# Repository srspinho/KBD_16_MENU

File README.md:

# RP2040 HID Remapper & System Monitor v3 ⌨️📺

Este projeto transforma um **Raspberry Pi Pico (RP2040 ou RP2350)** num intermediário entre o teclado USB e o PC. O teclado físico é ligado no Pico, e o Pico se apresenta ao PC como teclado + teclas de mídia + mouse. No caminho, ele remapeia atalhos, conta e analisa a digitação e mostra tudo num display TFT colorido de 160x80. Um joystick de 5 botões controla o menu.

## 🆕 Novidades da versão 3

**Correções**
- Menu: agora todos os itens dos submenus podem ser editados. Antes, só o primeiro de cada submenu funcionava.
- A contagem de setas, F8–F12, teclado numérico e `\` estava errada (deslocamento de bits ≥ 64) e foi corrigida.
- Fim das teclas "presas" no PC: os reports passam por uma fila e nenhum é descartado quando o USB está ocupado.
- Os dois núcleos não usam mais a mesma pilha USB ao mesmo tempo, o que podia travar o dispositivo.
- Os LEDs (Caps/Num Lock) são reaplicados quando o teclado é reconectado, e a desconexão do teclado agora é detectada.
- Remapeamento estável: soltar o AltGr antes do R não digita mais um "r".
- Screensavers sem desenho duplicado, sem cintilação e com as bolas sem acelerar até sumir. O Game of Life reinicia quando estabiliza.
- "Intervalo" do anti-bloqueio e "Brilho" passaram a funcionar. O escurecimento automático foi implementado.
- Configurações gravadas com versão + CRC, e só ao sair do menu (menos desgaste da flash e menos pausas no USB).
- Watchdog: se algo travar, o dispositivo reinicia sozinho.

**Novas funções**
- Páginas no monitor: Principal, Estatísticas, Top teclas, Pomodoro e Relógio.
- Total de teclas guardado na flash, contagem do dia, KPM (teclas por minuto) e recorde.
- Ranking das teclas mais usadas.
- Indicadores de Caps Lock e Num Lock na tela.
- Pomodoro, lembrete de pausa (prevenção de LER) e buzzer opcional.
- Camada Fn: com Caps Lock segurado, H/J/K/L viram setas, 1–0 viram F1–F10, etc.
- Macros: um atalho digita um texto.
- Relógio: ajuste pelo menu ou módulo RTC DS3231 opcional.
- Novos screensavers: Pong (simulação do jogo clássico, no lugar das Bolas), Estrelas em dobra espacial, foguetes nos Fogos e Relógio.
- Menu com auto-repetição acelerada, barra de rolagem, confirmação para ações perigosas e fechamento automático.
- "Modo gravação": entra no BOOTSEL pelo menu, sem precisar apertar o botão da placa.
- Testes automáticos da lógica do teclado, que rodam no PC (`test/host`).

## 🎮 Controles

| Onde | Botão | Ação |
|---|---|---|
| Monitor | **OK** | Abre o menu |
| Monitor | **← / →** | Troca de página |
| Página Pomodoro | **↑ / ↓** | Inicia/pausa · zera |
| Screensaver / tela escurecida | qualquer | Só acorda a tela |
| Menu | **↑ / ↓** | Move (segure para repetir) |
| Menu | **OK / →** | Entra · edita · liga/desliga · confirma |
| Menu | **←** | Volta (na raiz, fecha o menu) |
| Editando valor | **↑ / ↓** | Altera (segure para acelerar) |
| Editando valor | **OK / ← / →** | Termina a edição |

O menu fecha sozinho após 30 s sem uso e só grava na flash se algo mudou.

## 📋 Menu

```
CONFIGURACOES
├─ Screensaver   Tipo (lista) · Iniciar apos (min, 0 = nunca) · Trocar a cada (s)
│                Velocidade · Asteroides · Cores (%)
├─ Tela          Brilho · Brilho ocioso · Escurecer apos (s) · Girar 180
├─ Produtividade Anti-bloqueio · Intervalo (s) · Pomodoro >/|| · Pomodoro zerar
│                Foco (min) · Pausa (min) · Lembrete pausa (min, 0 = off)
├─ Teclado       Remapear · Camada Fn · Sinc. volume · Volume inicial
├─ Relogio       Hora · Minuto
├─ Estatisticas  Zerar sessao · Zerar tudo
├─ Sistema       Sobre · Reiniciar · Restaurar padrao · Modo gravacao
└─ Sair
```

## 🚀 Funcionalidades

### Teclado
- **Remapeamentos** (tabela em `keymap.cpp`):
  - `AltGr + R` → `\`
  - `AltGr + M` → `Ctrl + Shift + M` (microfone do Teams)
- **Macros:** um atalho digita um texto. Para criar uma, descomente o exemplo em `keymap.cpp`. Aceita letras, números, espaço, Enter, Tab e `. , - _ = + ! @ # $ % & * ( )`, que ficam na mesma posição no ABNT2 e no US.
- **Camada Fn** (desligada por padrão; ative em *Teclado > Camada Fn*). Segurando **Caps Lock**:
  - H/J/K/L → setas
  - Y/O → Home/End
  - U/N → PgUp/PgDn
  - Backspace → Delete
  - 1…0, -, = → F1…F12

  Um toque rápido no Caps Lock continua ligando e desligando o Caps.
- O teclado e o encoder de volume são lidos pelo descritor HID, o que deve servir para mais modelos de teclado.

### Monitor (páginas ← / →)
1. **Principal:**
   - Teclas de hoje (ou da sessão, se a hora não estiver ajustada)
   - KPM e gráfico dos últimos 60 s com escala automática
   - Barra de volume (e aviso de "MUDO")
   - LEDs Caps/Num, hora e barra de progresso do Pomodoro
2. **Estatísticas:** sessão, hoje, total (guardado na flash), KPM e recorde, tempo digitando e tempo ligado.
3. **Top teclas:** as 5 teclas mais usadas desde sempre. Só a quantidade de cada tecla é guardada, nunca a ordem do que foi digitado.
4. **Pomodoro:** contagem regressiva, fase (foco/pausa) e ciclos.
5. **Relógio.**

### Produtividade
- **Anti-bloqueio:** sem digitação pelo intervalo configurado, move o mouse 1 px e volta.
  > ⚠️ Em computadores corporativos, impedir o bloqueio de tela pode contrariar a política de segurança. Use com responsabilidade; a opção pode ser desligada.
- **Pomodoro** com alertas na tela (e no buzzer, se instalado).
- **Lembrete de pausa:** avisa depois de X minutos de digitação contínua. Cinco minutos sem digitar contam como pausa.

### Screensavers
Atari (arco-íris), Pong, Asteroides, Estrelas, Vida (Game of Life), Matrix, Pac-Man, Fogos, Aquário, Relógio, ou **Todos** (rotação automática).

### Relógio ⏰
O dispositivo **não consegue obter a hora do PC sem um programa rodando no PC**, porque o protocolo de teclado/mouse (HID) não transporta data e hora. Por isso há duas opções:
1. **Ajuste manual** em *Menu > Relogio*. A hora é mantida enquanto o dispositivo estiver energizado; se ele for desligado da USB, é preciso ajustar de novo.
2. **Módulo RTC DS3231** (opcional, barato, com bateria CR2032). É detectado sozinho no boot e mantém a hora mesmo desligado. Ao ajustar a hora pelo menu, o módulo também é atualizado.

## 🛠️ Hardware

### Placa de circuito impresso (KiCad)

A pasta [`hardware/`](hardware/README.md) tem o projeto KiCad completo de uma placa-base para o **Waveshare RP2350-Zero** (ou RP2040-Zero). Ela inclui:
- USB-A do teclado com fusível e proteção ESD;
- soquete do LCD e do joystick;
- RTC DS3231 com bateria;
- buzzer.

Também traz os Gerbers prontos para encomendar, a lista de componentes e o esquemático em PDF.

### Componentes

- **Microcontrolador:** RP2040 (testado no Waveshare RP2040-Zero) ou RP2350 (Waveshare RP2350-Zero).
- **Display:** TFT ST7735 0,96" 160x80 (SPI).
- **USB host:** conector USB-C/A para o teclado via PIO-USB.
- **Joystick de 5 botões** (4 direções + OK), com o pino comum no GND.
- *Opcional:* módulo RTC DS3231 e buzzer passivo.

### Pinagem

| Componente | GPIO | Observação |
|---|---|---|
| TFT_MISO | 12 | configurado no TFT_eSPI |
| TFT_MOSI (SDA) | 11 | |
| TFT_SCLK (SCL) | 10 | |
| TFT_CS | 13 | |
| TFT_DC | 14 | |
| TFT_RST | 15 | |
| **TFT_BLK** | **7** | Para o brilho funcionar. Ligado no 3V3, o brilho fica sempre no máximo (nesse caso use `PIN_BACKLIGHT -1`). |
| USB Host D+ | 0 | |
| USB Host D- | 1 | sempre D+ + 1 |
| USB VCC / GND | 5V / GND | |
| JOY_UP | 2 | |
| JOY_DOWN | 3 | |
| JOY_OK | 4 | |
| JOY_RIGHT | 5 | |
| JOY_LEFT | 6 | |
| RTC SDA *(opcional)* | 26 | I2C1 |
| RTC SCL *(opcional)* | 27 | I2C1 |
| Buzzer *(opcional)* | 8 | via transistor; `PIN_BUZZER` em `kbd_config.h` (-1 = sem buzzer) |

Todos os pinos (exceto os do display) ficam em **`kbd_config.h`**.

## 💻 Como compilar

1. Instale o core **Raspberry Pi Pico/RP2040/RP2350** (Earle Philhower) no Arduino IDE.
2. Bibliotecas:
   - [Pico-PIO-USB](https://github.com/sekigon-gonnoc/Pico-PIO-USB): USB host via PIO
   - [TFT_eSPI](https://github.com/Bodmer/TFT_eSPI): use um *User_Setup* para ST7735 160x80 (ex.: `Setup43_ST7735.h`) com os pinos da tabela acima
   - O Adafruit TinyUSB já vem com o core.
3. Em *Ferramentas*:
   - **Placa:** Waveshare RP2350 Zero (ou Waveshare RP2040 Zero)
   - **CPU Speed:** **120 MHz** (múltiplo de 12 MHz, exigido pelo USB host). No RP2350 o padrão é 150 MHz, que **não funciona**. Com um clock inválido, a tela mostra um erro explicando.
   - **USB Stack:** Adafruit TinyUSB
4. A pasta do projeto precisa ter o **mesmo nome do `.ino`**: `KBD_COLOR_16_MENU`.
5. Grave e conecte o teclado na porta USB host.

Para atualizar o firmware depois, use *Menu > Sistema > Modo gravacao* e copie o `.uf2` para a unidade `RPI-RP2`.

## 🧩 Estrutura do código

| Arquivo | Função |
|---|---|
| `KBD_COLOR_16_MENU.ino` | Só chama `app_*` (core 0) e `bridge_*` (core 1) |
| `kbd_config.h` | Pinos e opções de hardware |
| `usb_bridge.*` | **Core 1:** USB host, remapeamento, camada Fn, macros, fila de envio ao PC, LEDs |
| `shared.*` | Filas entre os núcleos (sem travas) |
| `keymap.*` | Tabelas de remapeamento, macros, camada e nomes das teclas |
| `app.*` | **Core 0:** lógica principal, anti-bloqueio, volume, alertas, watchdog |
| `ui.*` | Páginas do monitor, alertas e avisos |
| `menu.*` | Menu orientado a dados |
| `screensavers.*` | Screensavers numa tabela (adicionar um = uma linha) |
| `settings.*` | Preferências e armazenamento na flash (versão + CRC) |
| `stats.*` | Contagem, KPM, ranking de teclas |
| `pomodoro.*`, `clock.*`, `buttons.*`, `display.*` | Pomodoro, relógio/RTC, joystick, display/cores |
| `test/host/` | Testes que rodam no PC (`make`) |

## 🧪 Testes

A lógica do teclado (remapeamento, camada Fn, macros, fila sem perda, LEDs, mídia) e as estatísticas têm testes que rodam no PC, sem hardware:

```
cd test/host
make
```

## ⚠️ Limitações conhecidas

- **Volume:** o PC não informa o volume por HID. No boot, o volume do PC é levado a um valor conhecido (*Teclado > Volume inicial*), e a barra acompanha o encoder do teclado. Mudanças feitas pelo próprio PC não aparecem.
- **Hora:** veja a seção do relógio. Sem o RTC, a contagem "hoje" recomeça quando o dispositivo é desligado. O total e o ranking ficam na flash.
- Teclados no modo *boot* (6 teclas simultâneas) são suportados. Teclados que só funcionam em NKRO podem precisar estar no modo 6KRO.

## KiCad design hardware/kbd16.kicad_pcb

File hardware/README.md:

# Placa KBD16 (KiCad)

Placa-base para o **Waveshare RP2350-Zero**, que também aceita o **RP2040-Zero** (mesma pinagem). Ela junta numa só placa:

- a porta USB-A do teclado, com proteção;
- o LCD 0,96" 80x160;
- o joystick de 5 vias;
- o relógio RTC, com bateria;
- o buzzer.

A pinagem é a mesma do firmware (`kbd_config.h`), então não é preciso mudar nada no código.

| Frente | Verso |
|---|---|
|  |  |

- **Tamanho:** 86 × 52 mm, 2 camadas, cantos arredondados, 4 furos M3.
- **Regras:** trilhas de 0,25 mm (sinais) e 0,4–0,6 mm (alimentação), folga de 0,2 mm, vias de 0,8/0,4 mm. Qualquer fábrica comum (JLCPCB, PCBWay etc.) fabrica sem custo extra.
- **Planos de GND** nas duas camadas.
- **DRC** (verificação de regras do KiCad): sem erros e sem conexões faltando. Os únicos avisos são da serigrafia do USB-A, que fica para fora da borda de propósito.
- **Esquemático e PCB sincronizados** (verificado automaticamente).

## Arquivos

| Arquivo | Conteúdo |
|---|---|
| `kbd16.kicad_pro` / `.kicad_sch` / `.kicad_pcb` | Projeto KiCad (abre no KiCad 7 ou 8) |
| `lib/` | Símbolo e footprint do RP2350-Zero e footprint do soquete do LCD |
| `fab/kbd16_gerbers.zip` | **Gerbers + furação: é o arquivo que se envia para a fábrica** |
| `fab/kbd16_bom.csv` | Lista de componentes |
| `fab/kbd16_esquematico.pdf` | Esquemático em PDF |
| `fab/kbd16_posicao.csv` | Posição dos componentes (só para montagem pela fábrica) |
| `img/` | Imagens da placa |
| `tools/` | Scripts que geram tudo a partir de `tools/design.py` |

## Ligações (iguais às do firmware)

| Função | GPIO | Na placa |
|---|---|---|
| USB host D+ / D- (teclado) | GP0 / GP1 | J1 (USB-A), via R1/R2 (22 Ω) e proteção ESD U2 |
| Joystick cima / baixo / OK / dir / esq | GP2 / GP3 / GP4 / GP5 / GP6 | J3, com pull-ups de 10 kΩ (R4–R8) |
| Backlight do LCD (BLK) | GP7 | J2 pino 8, via R3 (100 Ω) |
| Buzzer | GP8 | Q1 + BZ1 (alimentado em 5 V) |
| LCD SCL / SDA / CS / DC / RES | GP10 / GP11 / GP13 / GP14 / GP15 | J2 |
| RTC SDA / SCL (I2C1) | GP26 / GP27 | U3 (DS3231), pull-ups de 4,7 kΩ |
| Livres | GP9, GP12, GP28, GP29 | (expansão futura) |

O 5 V do teclado sai do pino 5V do módulo (que vem do USB-C do PC) e passa pelo fusível rearmável F1 (500 mA).

## Montagem

Ordem sugerida, do componente mais baixo para o mais alto:

1. **SMD:**
   - resistores e capacitores 0805 (ilhas maiores, próprias para solda manual);
   - U2 (SOT-23-6), Q1 (SOT-23), D1 (SOD-123), F1 (1206);
   - U3 (SOIC-16), se for usar o RTC.
2. **Suporte da bateria BT1** (CR1220), se for usar o RTC.
3. **Barras fêmea:**
   - para o módulo: 2× 1x9 nas laterais e 1× 1x5 na fileira de baixo (GP9–GP13);
   - J2 (1x8) para o LCD;
   - J3 (1x6) para o joystick.

   Se preferir, solde o módulo direto na placa com barras macho, sem as fêmeas.
4. **USB-A J1 e buzzer BZ1** (THT).
5. **Módulo RP2350-Zero** com o USB-C virado para a borda de trás, onde está escrito *USB-C*.
6. **LCD:** encaixe no J2 com o display para cima, cobrindo a área marcada. A ordem dos pinos está na serigrafia: `GND VCC SCL SDA RES DC CS BLK`.

As partes opcionais podem ficar de fora sem afetar o resto:

| Opcional | Peças | Sem ela |
|---|---|---|
| **RTC** | U3, BT1, C3, R9, R10 | A hora é ajustada pelo menu e se perde ao desligar |
| **Buzzer** | BZ1, Q1, R11, R12, D1 | Os alertas aparecem só na tela |

> Se montar o U3, coloque a bateria: o DS3231 não deve ficar com o pino VBAT solto.

## ⚠️ Confira antes de encomendar

Alguns dados vieram de bibliotecas e fichas genéricas e não dá para confirmar sem as peças na mão. Imprima o PDF da placa em escala 1:1 e encoste as peças no papel:

1. **Módulo RP2350-Zero:** posição dos furos. A fileira de baixo (GP9–GP13) fica na mesma linha dos últimos pinos laterais.
2. **LCD:** a ordem dos 8 pinos do seu módulo (alguns fabricantes trocam) e o tamanho. O contorno de 30 × 24 mm é aproximado e está desenhado na camada F.Fab.
3. **Joystick:** a placa tem uma barra 1x6 na ordem `GND CIMA BAIXO ESQ DIR OK`. Ligue o comum do seu joystick no GND e cada direção no pino correspondente.
4. **USB-A:** footprint do Molex 67643 (THT horizontal, abas a 13,1 mm). A maioria das "USB-A fêmea 90° DIP" genéricas é compatível, mas confira as abas.

## Como encomendar

1. Envie `fab/kbd16_gerbers.zip` para a fábrica (ex.: JLCPCB → *Add gerber file*).
2. Opções:
   - 2 camadas, FR-4, 1,6 mm;
   - qualquer cor de máscara;
   - HASL (com ou sem chumbo).
   As demais podem ficar no padrão.
3. Os componentes estão em `fab/kbd16_bom.csv`. Todos são comuns: LCSC, Mouser, AliExpress etc.

## Firmware

- **Placa:** Waveshare RP2350 Zero.
- **USB Stack:** Adafruit TinyUSB.
- **CPU Speed: 120 MHz.** O padrão do RP2350 (150 MHz) **não funciona** com o USB host. Se esquecer, o firmware mostra um aviso na tela.
- O buzzer já está configurado no GP8 (`PIN_BUZZER` em `kbd_config.h`).

## Alterar a placa

Tudo é gerado a partir de `tools/design.py` (componentes, ligações e posições):

```
cd hardware/tools
python3 build_all.py
```

O script refaz em sequência:
- a biblioteca e o esquemático;
- a conferência entre os dois;
- a PCB e o roteamento;
- o DRC;
- os arquivos de fabricação e as imagens.

Ele precisa do KiCad 7 (`kicad-cli` e o módulo Python `pcbnew`); as imagens usam Node + Playwright e são opcionais.

O roteamento é feito por um roteador próprio e simples (`tools/router.py`, A* em grade). Se preferir, abra a placa no KiCad e refaça trilhas à mão: a partir daí, edite direto no KiCad em vez de rodar os scripts de novo.

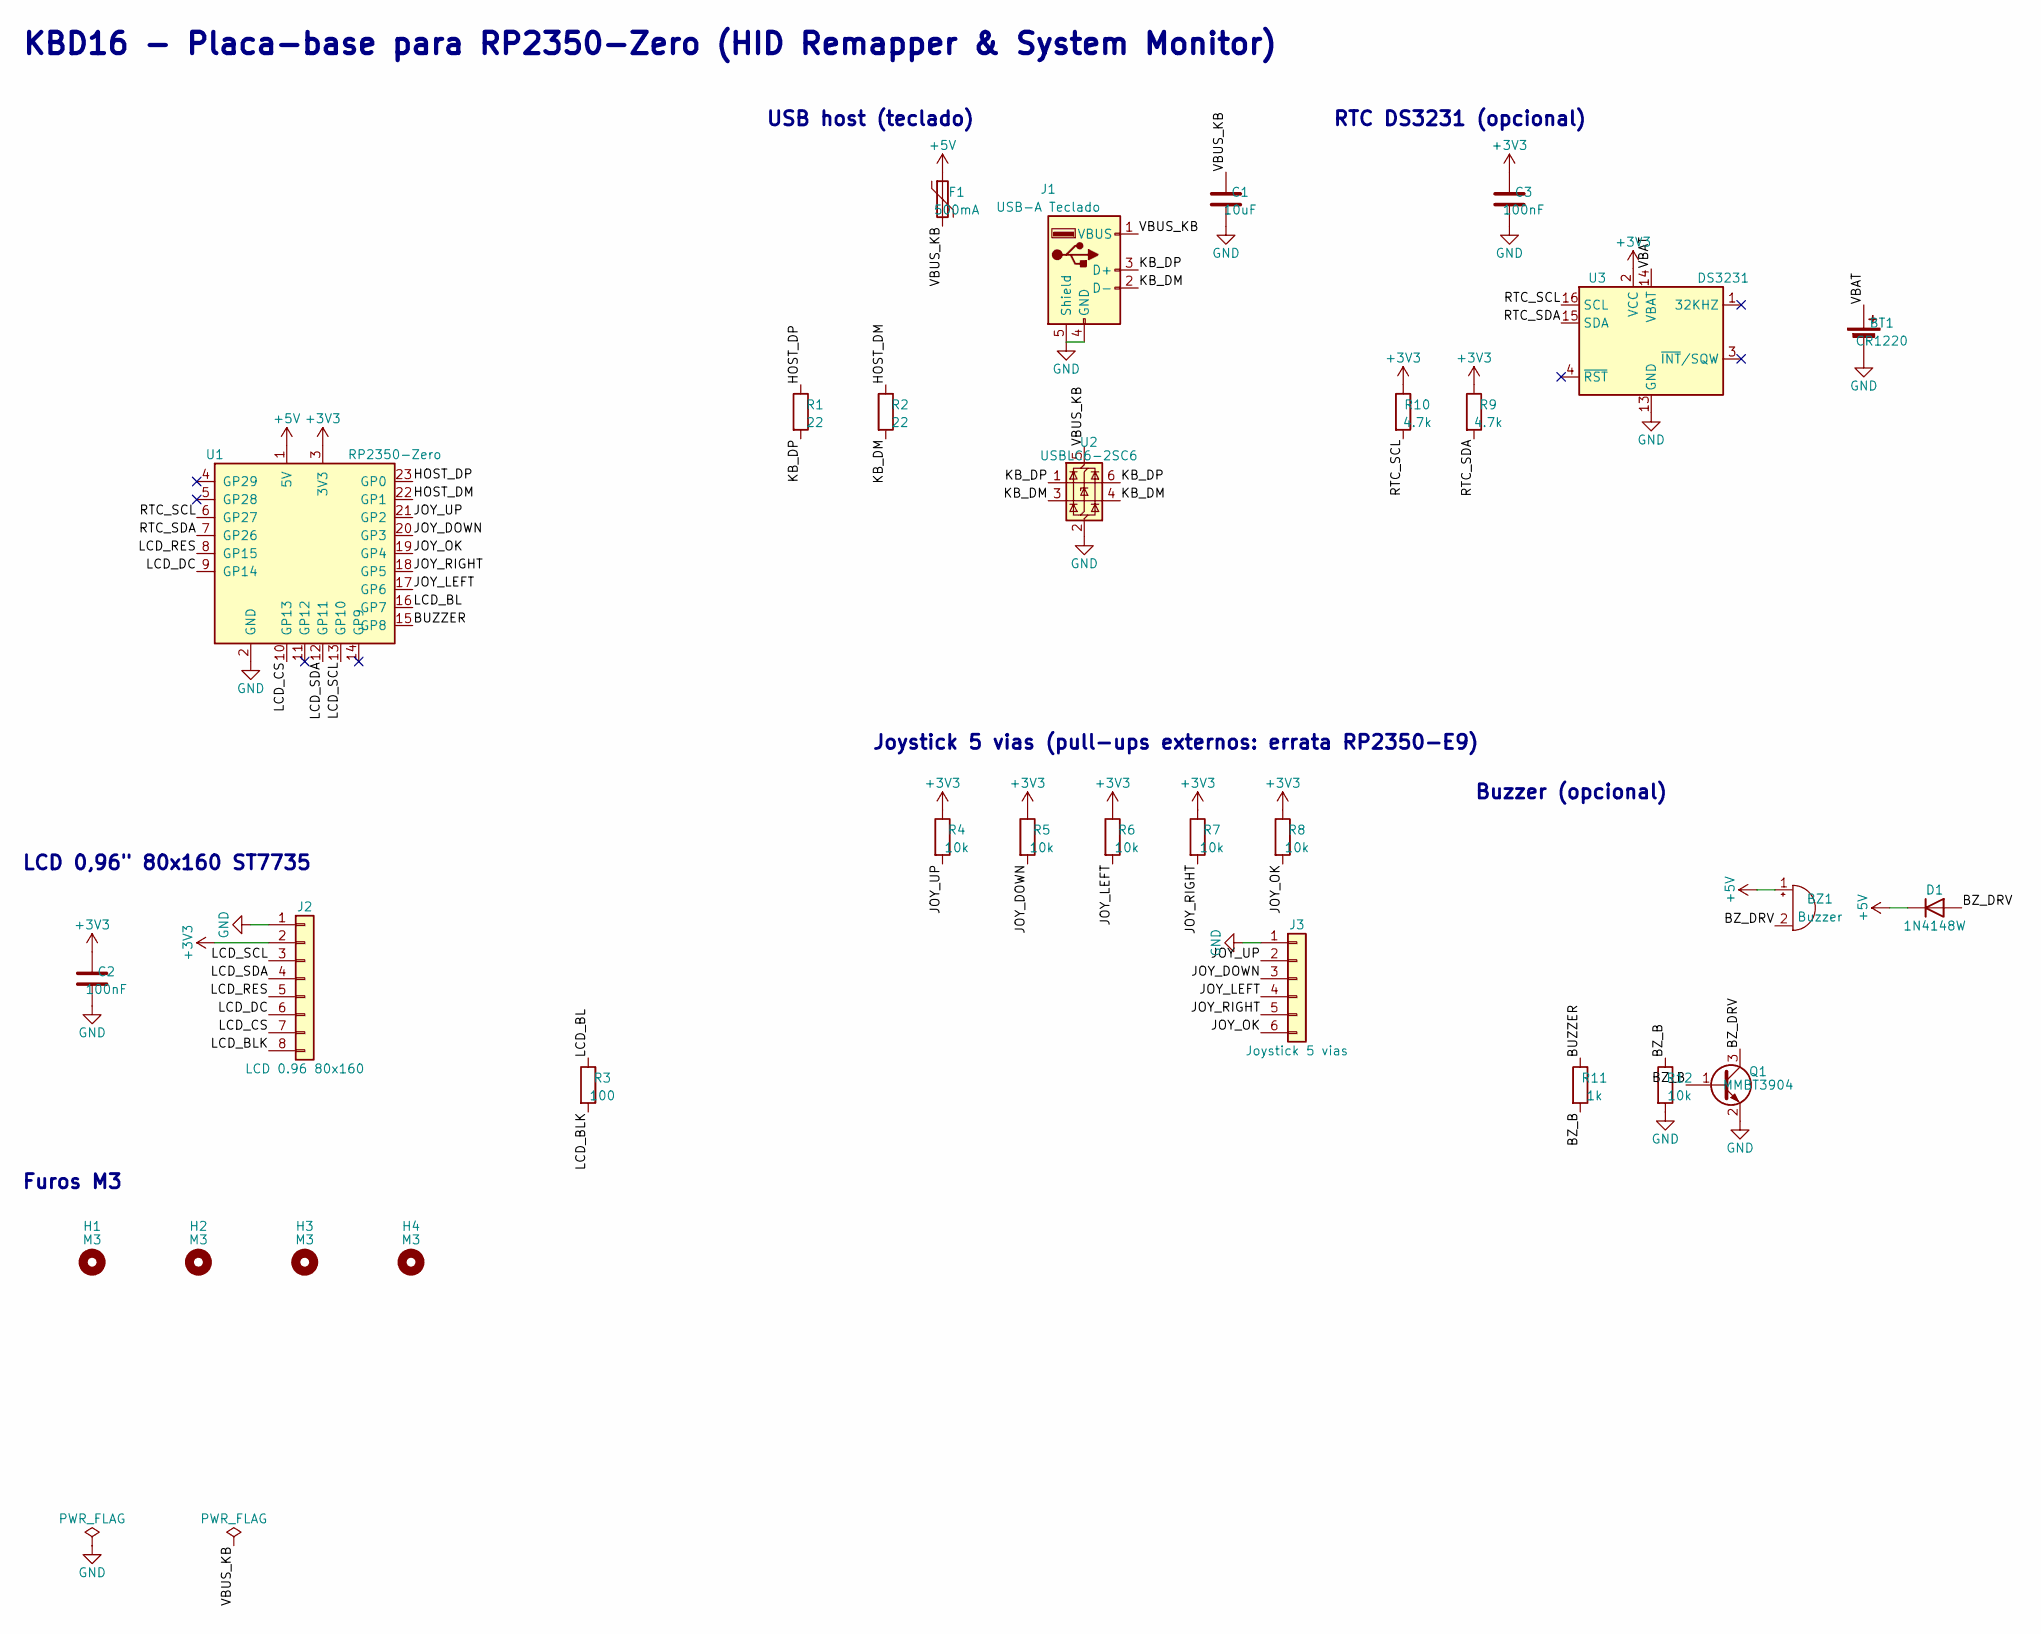
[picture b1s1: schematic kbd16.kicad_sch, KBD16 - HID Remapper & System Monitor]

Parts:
BT1: CR1220; BatteryHolder_Keystone_3000_1x12mm; MPN Keystone 3000
BZ1: Buzzer; Buzzer_12x9.5RM7.6; MPN TMB12A05 (passivo)
C1: 10uF; C_0805_2012Metric_Pad1.18x1.45mm_HandSolder
C2, C3: 100nF; C_0805_2012Metric_Pad1.18x1.45mm_HandSolder
D1: 1N4148W; D_SOD-123; MPN 1N4148W
F1: 500mA; Fuse_1206_3216Metric; MPN 1206L050
H1, H2, H3, H4: M3; MountingHole_3.2mm_M3
J1: USB-A Teclado; USB_A_Molex_67643_Horizontal; MPN Molex 67643-0910
J2: LCD 0.96 80x160; LCD_0.96_80x160_Socket
J3: Joystick 5 vias; PinSocket_1x06_P2.54mm_Vertical
Q1: MMBT3904; SOT-23; MPN MMBT3904
R1, R2: 22; R_0805_2012Metric_Pad1.20x1.40mm_HandSolder
R3: 100; R_0805_2012Metric_Pad1.20x1.40mm_HandSolder
R4, R5, R6, R7, R8, R12: 10k; R_0805_2012Metric_Pad1.20x1.40mm_HandSolder
R9, R10: 4.7k; R_0805_2012Metric_Pad1.20x1.40mm_HandSolder
R11: 1k; R_0805_2012Metric_Pad1.20x1.40mm_HandSolder
U1: RP2350-Zero; MPN Waveshare RP2350-Zero
U2: USBLC6-2SC6; SOT-23-6; MPN USBLC6-2SC6
U3: DS3231; SOIC-16W_7.5x10.3mm_P1.27mm; MPN DS3231SN#

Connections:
+3V3: C2.1, C3.1, J2.2, R4.1, R5.1, R6.1, R7.1, R8.1, R9.1, R10.1, U1.3 (3V3), U3.2 (VCC)
+5V: BZ1.1 (+), D1.1 (K), F1.1, U1.1 (5V)
/BUZZER: R11.1, U1.15 (GP8)
/BZ_B: Q1.1 (B), R11.2, R12.1
/BZ_DRV: BZ1.2 (-), D1.2 (A), Q1.3 (C)
/HOST_DM: R2.1, U1.22 (GP1)
/HOST_DP: R1.1, U1.23 (GP0)
/JOY_DOWN: J3.3, R5.2, U1.20 (GP3)
/JOY_LEFT: J3.4, R6.2, U1.17 (GP6)
/JOY_OK: J3.6, R8.2, U1.19 (GP4)
/JOY_RIGHT: J3.5, R7.2, U1.18 (GP5)
/JOY_UP: J3.2, R4.2, U1.21 (GP2)
/KB_DM: J1.2 (D-), R2.2, U2.3 (I/O2), U2.4 (I/O2)
/KB_DP: J1.3 (D+), R1.2, U2.1 (I/O1), U2.6 (I/O1)
/LCD_BL: R3.1, U1.16 (GP7)
/LCD_BLK: J2.8, R3.2
/LCD_CS: J2.7, U1.10 (GP13)
/LCD_DC: J2.6, U1.9 (GP14)
/LCD_RES: J2.5, U1.8 (GP15)
/LCD_SCL: J2.3, U1.13 (GP10)
/LCD_SDA: J2.4, U1.12 (GP11)
/RTC_SCL: R10.2, U1.6 (GP27), U3.16 (SCL)
/RTC_SDA: R9.2, U1.7 (GP26), U3.15 (SDA)
/VBAT: BT1.1 (+), U3.14 (VBAT)
/VBUS_KB: C1.1, F1.2, J1.1 (VBUS), U2.5 (VBUS)
GND: BT1.2 (-), C1.2, C2.2, C3.2, J1.4 (GND), J1.5 (Shield), J2.1, J3.1, Q1.2 (E), R12.2, U1.2 (GND), U2.2 (GND), U3.5 (GND), U3.6 (GND), U3.7 (GND), U3.8 (GND), U3.9 (GND), U3.10 (GND), U3.11 (GND), U3.12 (GND), U3.13 (GND)

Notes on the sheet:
KBD16 - Placa-base para RP2350-Zero (HID Remapper & System Monitor)
USB host (teclado)
LCD 0,96" 80x160 ST7735
Joystick 5 vias (pull-ups externos: errata RP2350-E9)
RTC DS3231 (opcional)
Buzzer (opcional)
Furos M3

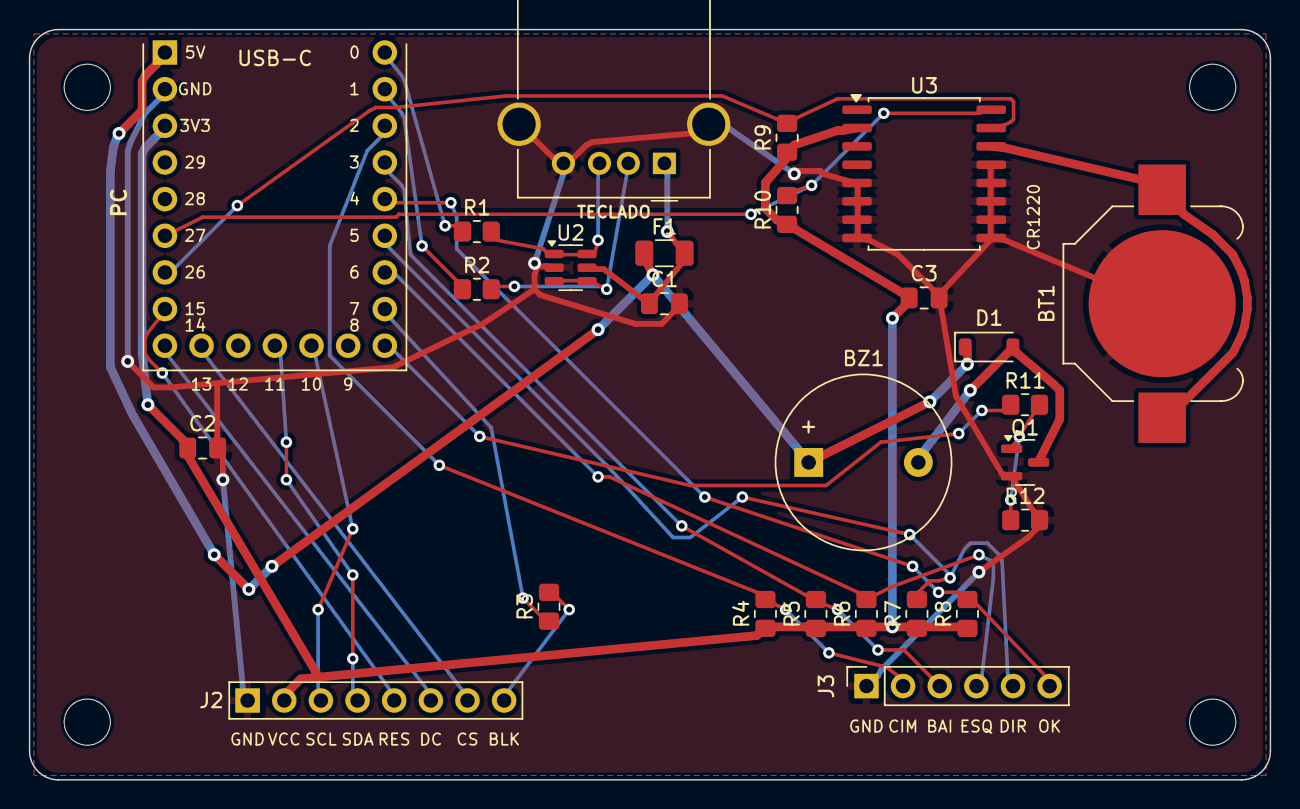
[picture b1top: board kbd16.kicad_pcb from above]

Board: 2 copper layers, 86.0 x 52.0 mm, 30 parts (0 on the bottom side), 26 nets.

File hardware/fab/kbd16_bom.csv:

Qtd,Referências,Valor,Descrição,Peça sugerida,Footprint
1,U1,RP2350-Zero,Waveshare RP2350-Zero (ou RP2040-Zero),Waveshare RP2350-Zero,RP2350-Zero
1,J1,USB-A Teclado,Receptáculo USB-A horizontal THT,Molex 67643-0910,USB_A_Molex_67643_Horizontal
1,F1,500mA,Fusível rearmável 500 mA hold,1206L050,Fuse_1206_3216Metric
1,C1,10uF,Capacitor cerâmico 10 µF 10 V X5R,,C_0805_2012Metric_Pad1.18x1.45mm_HandSolder
1,U2,USBLC6-2SC6,Proteção ESD USB,USBLC6-2SC6,SOT-23-6
2,R1 R2,22,Resistor série D+ / Resistor série D-,,R_0805_2012Metric_Pad1.20x1.40mm_HandSolder
1,J2,LCD 0.96 80x160,"Barra fêmea 1x8 2,54 mm para o módulo LCD ST7735",,LCD_0.96_80x160_Socket
1,R3,100,Resistor série do backlight (GPIO7 -> BLK),,R_0805_2012Metric_Pad1.20x1.40mm_HandSolder
2,C2 C3,100nF,Desacoplamento 3V3 do LCD / Desacoplamento do RTC,,C_0805_2012Metric_Pad1.18x1.45mm_HandSolder
1,J3,Joystick 5 vias,"Barra fêmea 1x6 para o joystick (COM, CIMA, BAIXO, ESQ, DIR, OK)",,PinSocket_1x06_P2.54mm_Vertical
6,R4 R5 R6 R7 R8 R12,10k,Pull-up do joystick / Pull-down de base (buzzer mudo no boot),,R_0805_2012Metric_Pad1.20x1.40mm_HandSolder
1,U3,DS3231,RTC DS3231SN ou DS3231M (opcional),DS3231SN#,SOIC-16W_7.5x10.3mm_P1.27mm
1,BT1,CR1220,Suporte de bateria CR1220,Keystone 3000,BatteryHolder_Keystone_3000_1x12mm
2,R9 R10,4.7k,Pull-up I2C SDA / Pull-up I2C SCL,,R_0805_2012Metric_Pad1.20x1.40mm_HandSolder
1,BZ1,Buzzer,"Buzzer magnético passivo 12 mm, 5 V",TMB12A05 (passivo),Buzzer_12x9.5RM7.6
1,Q1,MMBT3904,Driver do buzzer,MMBT3904,SOT-23
1,R11,1k,Resistor de base,,R_0805_2012Metric_Pad1.20x1.40mm_HandSolder
1,D1,1N4148W,Diodo de roda livre do buzzer,1N4148W,D_SOD-123
2,(U1),"1x9 fêmea 2,54 mm",Barras para encaixar o RP2350-Zero (ou solde o módulo direto com barras macho),,
1,(U1),"1x5 fêmea 2,54 mm",Barra da fileira de baixo do RP2350-Zero (GP9-GP13),,
1,(BT1),CR1220,Bateria do RTC (opcional),,
4,(H1-H4),M3,Parafusos M3 + espaçadores de 10 mm,,

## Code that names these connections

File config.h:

/*********************************************************************
 * config.h - Configuração de HARDWARE e opções de compilação
 *
 * Tudo que depende da sua montagem física fica aqui. As preferências
 * do usuário (brilho, screensaver, etc.) ficam em settings.h e são
 * ajustadas pelo menu e gravadas na flash.
 *********************************************************************/
#ifndef CONFIG_H
#define CONFIG_H

#define FW_VERSION "3.0"

// ==================== USB HOST (PIO-USB) ====================
// D+ do teclado. O D- é obrigatoriamente o pino seguinte (D+ + 1).
#define PIN_USB_HOST_DP 0

// Pino que liga a alimentação 5V do teclado (só em placas que têm
// esse controle). No RP2040-Zero o 5V vem direto do VBUS: deixe -1.
#define PIN_5V_EN       -1
#define PIN_5V_EN_STATE 1

// ==================== JOYSTICK (5 botões, ativos em LOW) ====================
// O pino comum do joystick vai no GND.
#define JOY_UP    2
#define JOY_DOWN  3
#define JOY_OK    4
#define JOY_RIGHT 5
#define JOY_LEFT  6

// ==================== DISPLAY ====================
// Os pinos SPI do display são configurados no TFT_eSPI (User_Setup).
// Backlight: ligue o pino BLK do display neste GPIO para o brilho e o
// escurecimento automático funcionarem. Se o BLK estiver ligado direto
// no 3V3, use -1 (o display fica sempre no brilho máximo).
// Se o seu User_Setup do TFT_eSPI definir TFT_BL, ele tem prioridade.
#define PIN_BACKLIGHT 7

// ==================== RELÓGIO (opcional) ====================
// Módulo RTC DS3231 (I2C) para manter a hora mesmo sem energia.
// Sem o módulo, a hora é ajustada pelo menu e mantida enquanto o
// dispositivo estiver ligado. A detecção é automática.
#define RTC_ENABLED 1
#define PIN_RTC_SDA 26   // I2C1 SDA
#define PIN_RTC_SCL 27   // I2C1 SCL

// ==================== BUZZER (opcional) ====================
// Buzzer passivo para os alertas (Pomodoro / pausa). -1 = sem buzzer.
// Na placa KiCad (pasta hardware/) o buzzer fica no GP8, via transistor.
#define PIN_BUZZER 8

// ==================== TECLA DA CAMADA (Fn) ====================
// Segurando esta tecla, H/J/K/L viram setas etc. (ver keymap.cpp).
// Um toque rápido nela continua funcionando normalmente.
// Ativar/desativar pelo menu: Teclado > Camada Fn.
#define LAYER_KEY HID_KEY_CAPS_LOCK

// ==================== TELA ====================
#define SCREEN_W 160
#define SCREEN_H 80

// ==================== DEPURAÇÃO ====================
// Descomente para ver mensagens na porta serial (CDC).
// #define DEBUG_LOG
#ifdef DEBUG_LOG
  #define LOG(...) Serial.printf(__VA_ARGS__)
#else
  #define LOG(...) do {} while (0)
#endif

#endif

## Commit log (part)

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2026-06-07 Versão Inicial
    Add initial project details and library requirements.
2026-06-07 Versão inicial
2026-06-07 Clean up TFT pin definitions in README
    Removed unused TFT pin definitions and updated pinout table.
2026-06-07 Fix formatting issues in README.md
